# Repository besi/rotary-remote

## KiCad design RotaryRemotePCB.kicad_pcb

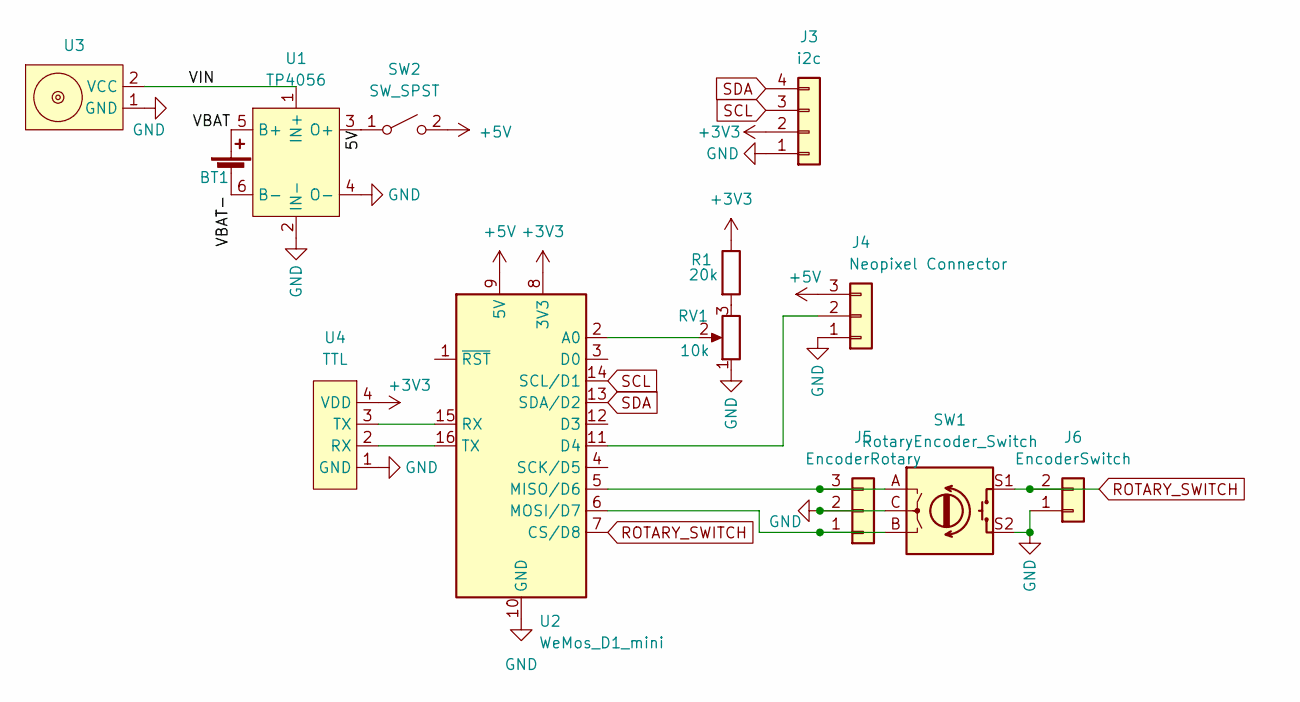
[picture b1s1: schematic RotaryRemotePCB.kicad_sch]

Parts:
BT1: Battery_Cell; JST_EH_S2B-EH_1x02_P2.50mm_Horizontal
J3: i2c; PinHeader_1x04_P2.54mm_Vertical
J4: Neopixel Connector; PinHeader_1x03_P2.54mm_Horizontal
J5: EncoderRotary; PinHeader_1x03_P2.54mm_Vertical
J6: EncoderSwitch; PinHeader_1x02_P2.54mm_Vertical
R1: 20k; R_Axial_DIN0207_L6.3mm_D2.5mm_P7.62mm_Horizontal
RV1: 10k; Potentiometer_Piher_PT-6-V_Vertical
SW1: RotaryEncoder_Switch
SW2: SW_SPST; SW_SPDT_CK-JS102011SAQN
U1: TP4056
U2: WeMos_D1_mini; WEMOS_D1_mini_light
U3: magnetic-charger
U4: TTL; PinHeader_1x04_P2.54mm_Vertical

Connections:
+3V3: J3.2, R1.1, U2.8 (3V3), U4.4 (VDD)
+5V: J4.3, SW2.2 (B), U2.9 (5V)
/5V: SW2.1 (A), U1.3 (O+)
/VBAT: BT1.1 (+), U1.5 (B+)
/VBAT-: BT1.2 (-), U1.6 (B-)
/VIN: U1.1 (IN+), U3.2 (VCC)
GND: J3.1, J4.1, J5.2, J6.1, RV1.1, SW1.C, SW1.S2, U1.2 (IN-), U1.4 (O-), U2.10 (GND), U3.1 (GND), U4.1 (GND)
unnamed: J4.2, U2.11 (D4)
unnamed: J5.1, SW1.B, U2.6 (MOSI/D7)
unnamed: J5.3, SW1.A, U2.5 (MISO/D6)
unnamed: R1.2, RV1.3
unnamed: RV1.2, U2.2 (A0)
unnamed: U2.15 (RX), U4.3 (TX)
unnamed: U2.16 (TX), U4.2 (RX)
ROTARY_SWITCH: J6.2, SW1.S1, U2.7 (CS/D8)
SCL: J3.3, U2.14 (SCL/D1)
SDA: J3.4, U2.13 (SDA/D2)

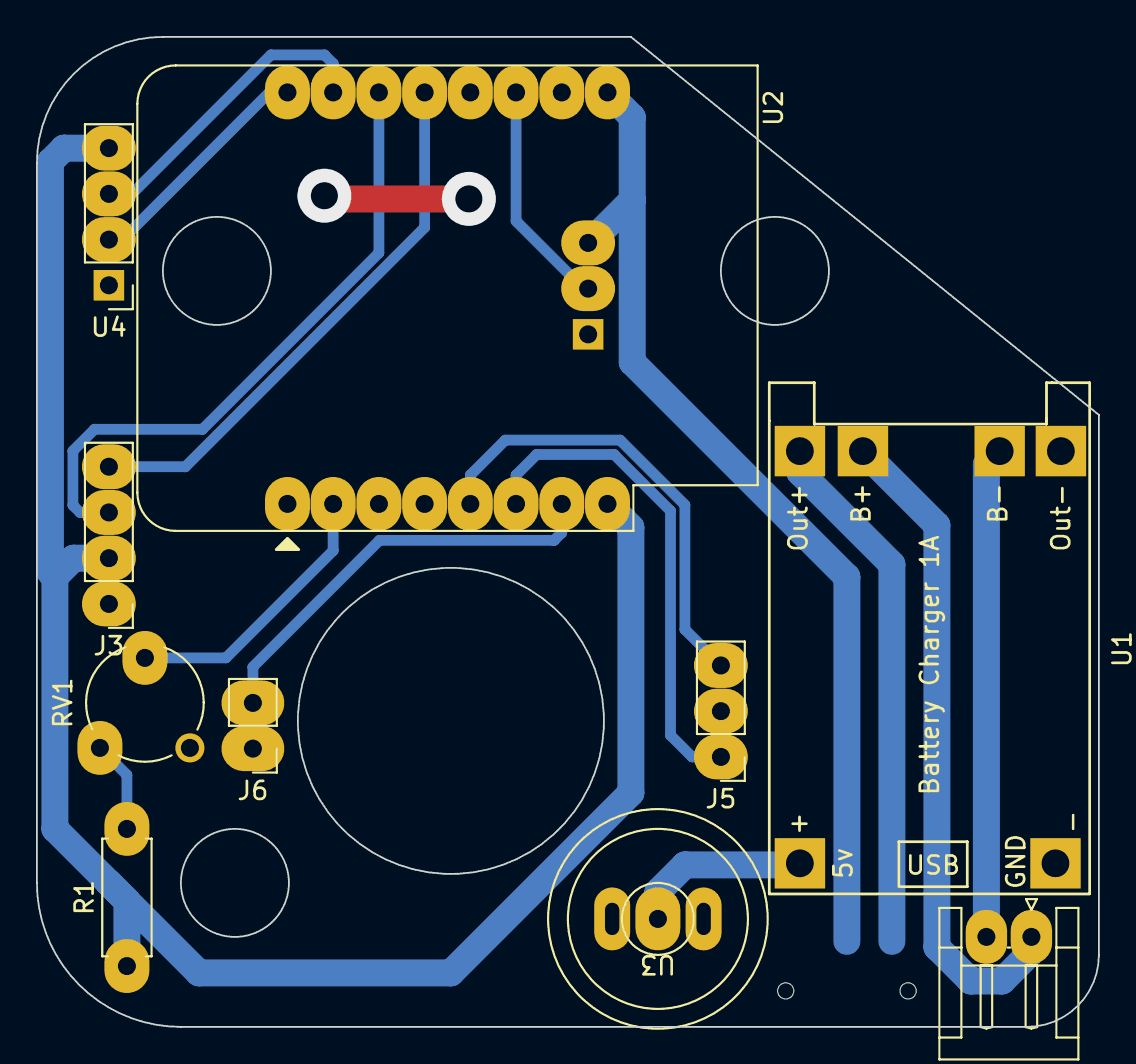
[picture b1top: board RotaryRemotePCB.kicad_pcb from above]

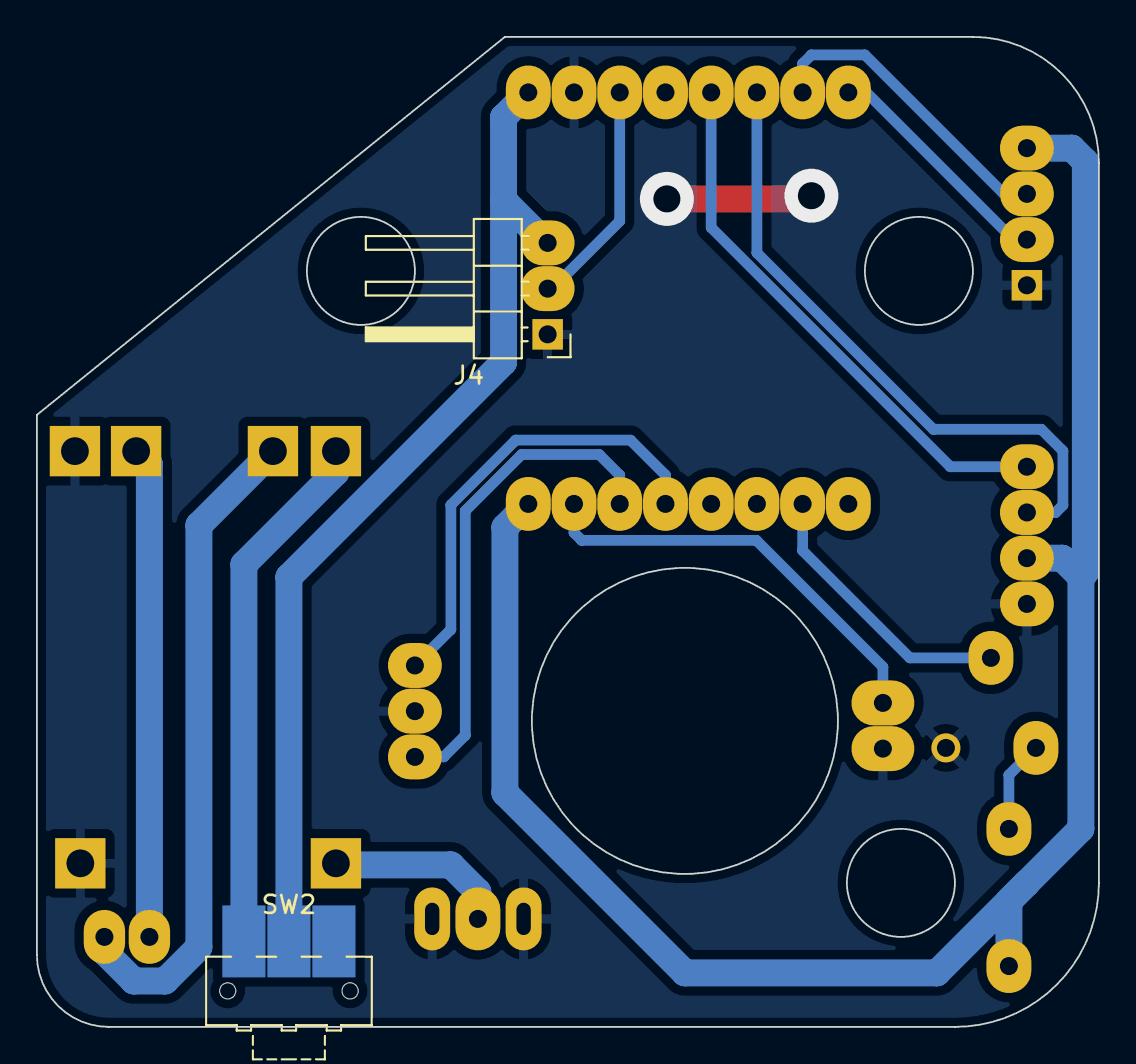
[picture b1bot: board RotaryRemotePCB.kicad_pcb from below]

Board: 2 copper layers, 59.0 x 55.0 mm, 12 parts (2 on the bottom side), 17 nets.

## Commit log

2023-02-19 Add git submodule
2023-02-19 Add FTDI connector
2023-02-19 Update I2C Bus
2023-02-19 Prepare for milling
2023-02-19 Rearrange the sockets
2023-02-20 Make corner radiuses
